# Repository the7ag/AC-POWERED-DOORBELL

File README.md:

# ESP32 AC Powered with Node.js API to data log

This project uses an **ESP32** microcontroller to send signal data (when a digital pin goes HIGH) to a **Node.js** backend API. The backend uses **MongoDB** to store user data and the signal data. The ESP32 device sends the data to the server only when the signal on a specific pin goes HIGH, with API key-based authentication.

## Table of Contents
- [Project Overview](#project-overview)
- [Hardware Requirements](#hardware-requirements)
- [Software Requirements](#software-requirements)
- [Project Setup](#project-setup)
- [Backend API Structure](#backend-api-structure)
- [ESP32 Setup](#esp32-setup)
- [Database Schema](#database-schema)
- [API Endpoints](#api-endpoints)
- [Testing](#testing)
- [Images](#images)

## Project Overview
This project allows you to authenticate a user and send digital signal data from the ESP32 to a backend server using an API key. When the pin state of a digital input (connected to pin 13) goes HIGH, the ESP32 sends a POST request to the backend API with a timestamp and pin state.

The backend server:
1. Validates the API key sent with each request.
2. Stores signal data in the **SignalData** collection in MongoDB.
3. Associates the data with a user based on their **unique ID** and **API key**.

## Hardware Requirements
- **ESP32 Development Board**
- **Jumper wires** for connecting to external pins
- A breadboard (optional)

### Connections:
- **Pin 13**: Connected to a digital signal source (e.g., a button or sensor)

## Software Requirements
- **Arduino IDE** with the ESP32 board package installed
- **Node.js** and **npm** for running the backend server
- **MongoDB** (local or cloud) to store user and signal data
- **Arduino JSON** library for handling JSON data in the ESP32

## Project Setup

### 1. Clone the Repository
Clone the repository to your local machine:
```bash
git clone https://github.com/yourusername/esp32-signal-data-logger.git
```

### 2. Set Up the Backend API

#### Backend Requirements:
- **Node.js** and **npm** installed
- **MongoDB** running locally or using a cloud service (e.g., MongoDB Atlas)

To set up the backend:
1. Navigate to the `backend` directory:
   ```bash
   cd backend
   ```

2. Install the required dependencies:
   ```bash
   npm install
   ```

3. Start the backend server:
   ```bash
   npm start
   ```

The backend API will be accessible at `http://localhost:5000`.

### 3. Set Up the ESP32

#### ESP32 Code:
1. Open the Arduino IDE and set the board to **ESP32**.
2. Install the **ArduinoJson** library using the Library Manager.
3. Open the ESP32 code, modify the Wi-Fi credentials and backend URL as needed.
4. Upload the code to the ESP32.

### 4. Configure MongoDB
Ensure that MongoDB is running, and update the database connection settings in the backend code (if necessary).

## Backend API Structure

The backend consists of two main collections in MongoDB:
1. **Users**: Stores the user's `uniqueID` and their `apiKey`.
2. **SignalData**: Stores the signal data, including the `timestamp` and `pinState`, linked to the user by their `uniqueID`.

### Database Models:
#### User Schema:
- **uniqueID**: A unique identifier for each user (e.g., from ESP32).
- **apiKey**: A unique API key for the user.

#### SignalData Schema:
- **userID**: The `uniqueID` of the user who owns the signal data.
- **timestamp**: The timestamp when the pin state went HIGH.
- **pinState**: The state of the pin (HIGH/LOW).

## API Endpoints

### 1. **Authentication (POST /auth)**
- **Description**: Authenticates the user and returns an API key.
- **Request Body**:
  ```json
  {
    "unique_id": "USER_UNIQUE_ID"
  }
  ```
- **Response**:
  ```json
  {
    "api_key": "USER_API_KEY"
  }
  ```

### 2. **Save Signal Data (POST /data)**
- **Description**: Saves the signal data when the pin goes HIGH.
- **Request Headers**:
  - **API-Key**: The user's API key.
- **Request Body**:
  ```json
  {
    "timestamp": "timestamp_value",
    "pin_state": "HIGH"
  }
  ```
- **Response**:
  ```json
  {
    "message": "Signal data saved successfully"
  }
  ```

## Testing

### 1. Testing the API:
You can use tools like **Postman** or **curl** to test the API endpoints.

- **Authenticate User**: Send a `POST` request to `/auth` with the `unique_id`.
- **Submit Signal Data**: Send a `POST` request to `/data` with the API key in the headers and the signal data in the body.

### 2. Testing the ESP32:
- Once the ESP32 is running, it will automatically connect to the Wi-Fi, authenticate with the backend, and send signal data when the digital pin goes HIGH.

## Images

### 1. ESP32 Pin Connection Diagram

### 2. Entire Board

## License
This project is licensed under the MIT License - see the [LICENSE](./LICENSE) file for details.

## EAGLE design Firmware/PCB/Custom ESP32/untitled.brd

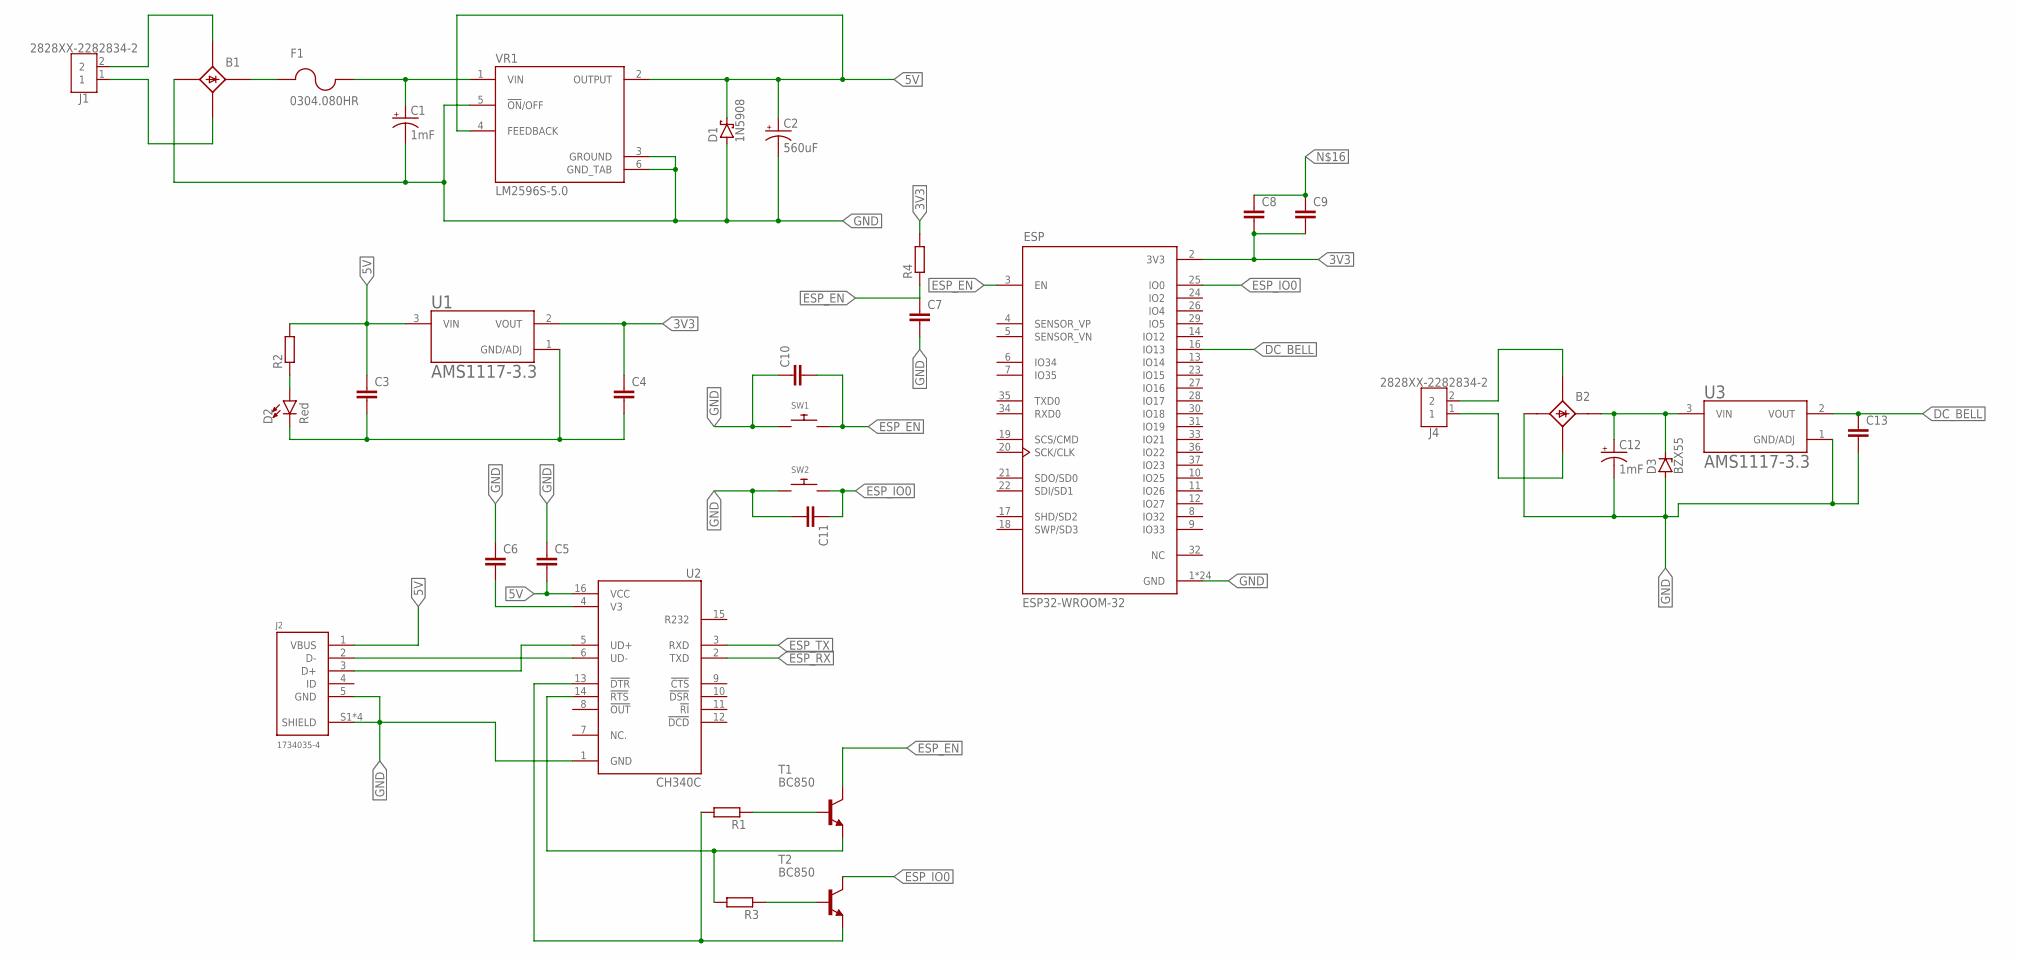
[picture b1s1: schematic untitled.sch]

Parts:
B1, B2: B25A-
C1, C12: 1mF; CPOL-RADIAL-5MM-10MM
C2: 560uF; PANASONIC_G
C3, C4, C5, C6, C7, C8, C9, C10, C11, C13: C-EUC1206K; C1206K
D1: 1N5908; C4111-15
D2: Red; LED-0603
D3: BZX55; DO35Z10
ESP: ESP32-WROOM-32; MODULE_ESP32-WROOM-32
F1: 0304.080HR
J1, J4: 2828XX-2282834-2; TERMBLK_254-2N
J2: 1734035-4
R1, R2, R3, R4: R-EU_R5025W; R5025W
SW1, SW2: SWITCH_PUSHBUTTONSOFTTOUCHSMD_SJ; PUSHBUTTON_SMD_SJ
T1, T2: BC850; SOT23
U1, U3: AMS1117-3.3; SOT229P700X180-4N
U2: CH340C; SOIC127P600X180-16N
VR1: LM2596S-5.0; TO170P1524X483-6N

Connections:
3V3: C4.1, C8.2, C9.2, ESP.2 (3V3), R4.2, U1.2 (VOUT)
5V: C2.+, C3.1, C5.2, D1.C, J2.1 (VBUS), R2.2, U1.3 (VIN), U2.16 (VCC), VR1.2 (OUTPUT), VR1.4 (FEEDBACK)
DC_BELL: C13.1, ESP.16 (IO13), U3.2 (VOUT)
ESP_EN: C7.1, C10.2, ESP.3 (EN), R4.1, SW1.P$2, T1.3 (C)
ESP_IO0: C11.1, ESP.25 (IO0), SW2.P$2, T2.3 (C)
ESP_RX: U2.2 (TXD)
ESP_TX: U2.3 (RXD)
GND: B1.-1 (-), B2.-1 (-), C1.-, C2.-, C5.1, C6.1, C7.2, C10.1, C11.2, C12.-, C13.2, D1.A, D3.A, ESP.1 (GND), ESP.15 (GND), ESP.38 (GND), ESP.39_1 (GND), ESP.39_2 (GND), ESP.39_3 (GND), ESP.39_4 (GND), ESP.39_5 (GND), ESP.39_6 (GND), ESP.39_7 (GND), ESP.39_8 (GND), ESP.39_9 (GND), ESP.39_10 (GND), ESP.39_11 (GND), ESP.39_12 (GND), ESP.39_13 (GND), ESP.39_14 (GND), ESP.39_15 (GND), ESP.39_16 (GND), ESP.39_17 (GND), ESP.39_18 (GND), ESP.39_19 (GND), ESP.39_20 (GND), ESP.39_21 (GND), J2.5 (GND), J2.S1 (SHIELD), J2.S2 (SHIELD), J2.S3 (SHIELD), J2.S4 (SHIELD), SW1.P$1, SW2.P$1, U2.1 (GND), U3.1 (GND/ADJ), VR1.3 (GROUND), VR1.5 (!ON!/OFF), VR1.6 (GND_TAB)
unnamed: B1.AC1- (AC1), J1.2
unnamed: B1.AC2- (AC2), J1.1
unnamed: B1.+1 (+), F1.1
unnamed: C1.+, F1.2, VR1.1 (VIN)
unnamed: D2.A, R2.1
unnamed: C3.2, C4.2, D2.C, U1.1 (GND/ADJ)
unnamed: J2.3 (D+), U2.5 (UD+)
unnamed: J2.2 (D-), U2.6 (UD-)
unnamed: B2.AC1- (AC1), J4.2
unnamed: B2.AC2- (AC2), J4.1
unnamed: C6.2, U2.4 (V3)
unnamed: R1.1, T1.1 (B)
unnamed: R3.1, T2.1 (B)
unnamed: R3.2, T1.2 (E), U2.14 (!RTS)
unnamed: R1.2, T2.2 (E), U2.13 (!DTR)
unnamed: C8.1, C9.1
unnamed: B2.+1 (+), C12.+, D3.C, U3.3 (VIN)

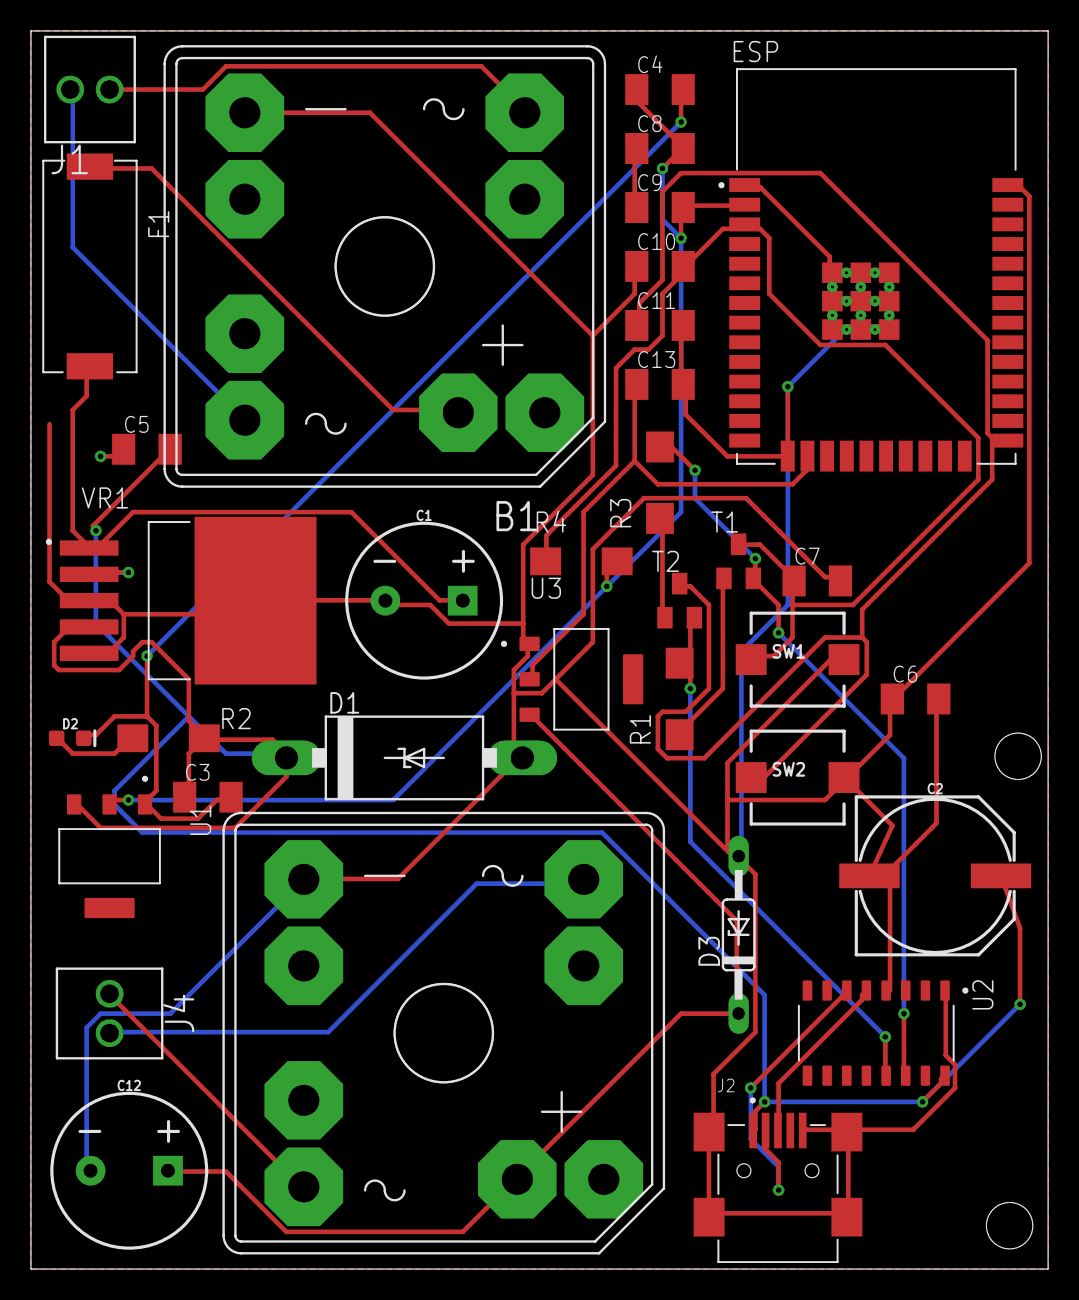
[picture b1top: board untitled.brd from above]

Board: 2 copper layers, 65.7 x 80.0 mm, 35 parts (0 on the bottom side), 23 nets.

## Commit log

2024-11-26 refactored for nullPTR and docstrings
2024-11-26 Added PCB Files

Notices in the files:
parts and their libraries:
SparkFun-Capacitors: Licensing: Creative Commons ShareAlike 4.0 International - https://creativecommons.org/licenses/by-sa/4.0
